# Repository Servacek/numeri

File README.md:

# Numitronové Hodiny - Numeri

Digitálne hodiny využívajúce na zobrazovanie času staré sovietske numitrony IV-9. Podporujú tiež pripojenie rádiového modulu DCF77 pre automatické nastavovanie času podľa atomových hodín z Mainflingenu.

https://github.com/user-attachments/assets/5947127a-6d7e-4e79-9d8d-92cfa04d009d

## DCF77 Anténa

Vlastná 140 mm anténa sa zdá byť najefektívnejšie a cenovo najdostupnejšie riešenie. Čim väčšia feritová tyč, tým lepšie.

## Schéma zapojeniaa návrh plošného spoja

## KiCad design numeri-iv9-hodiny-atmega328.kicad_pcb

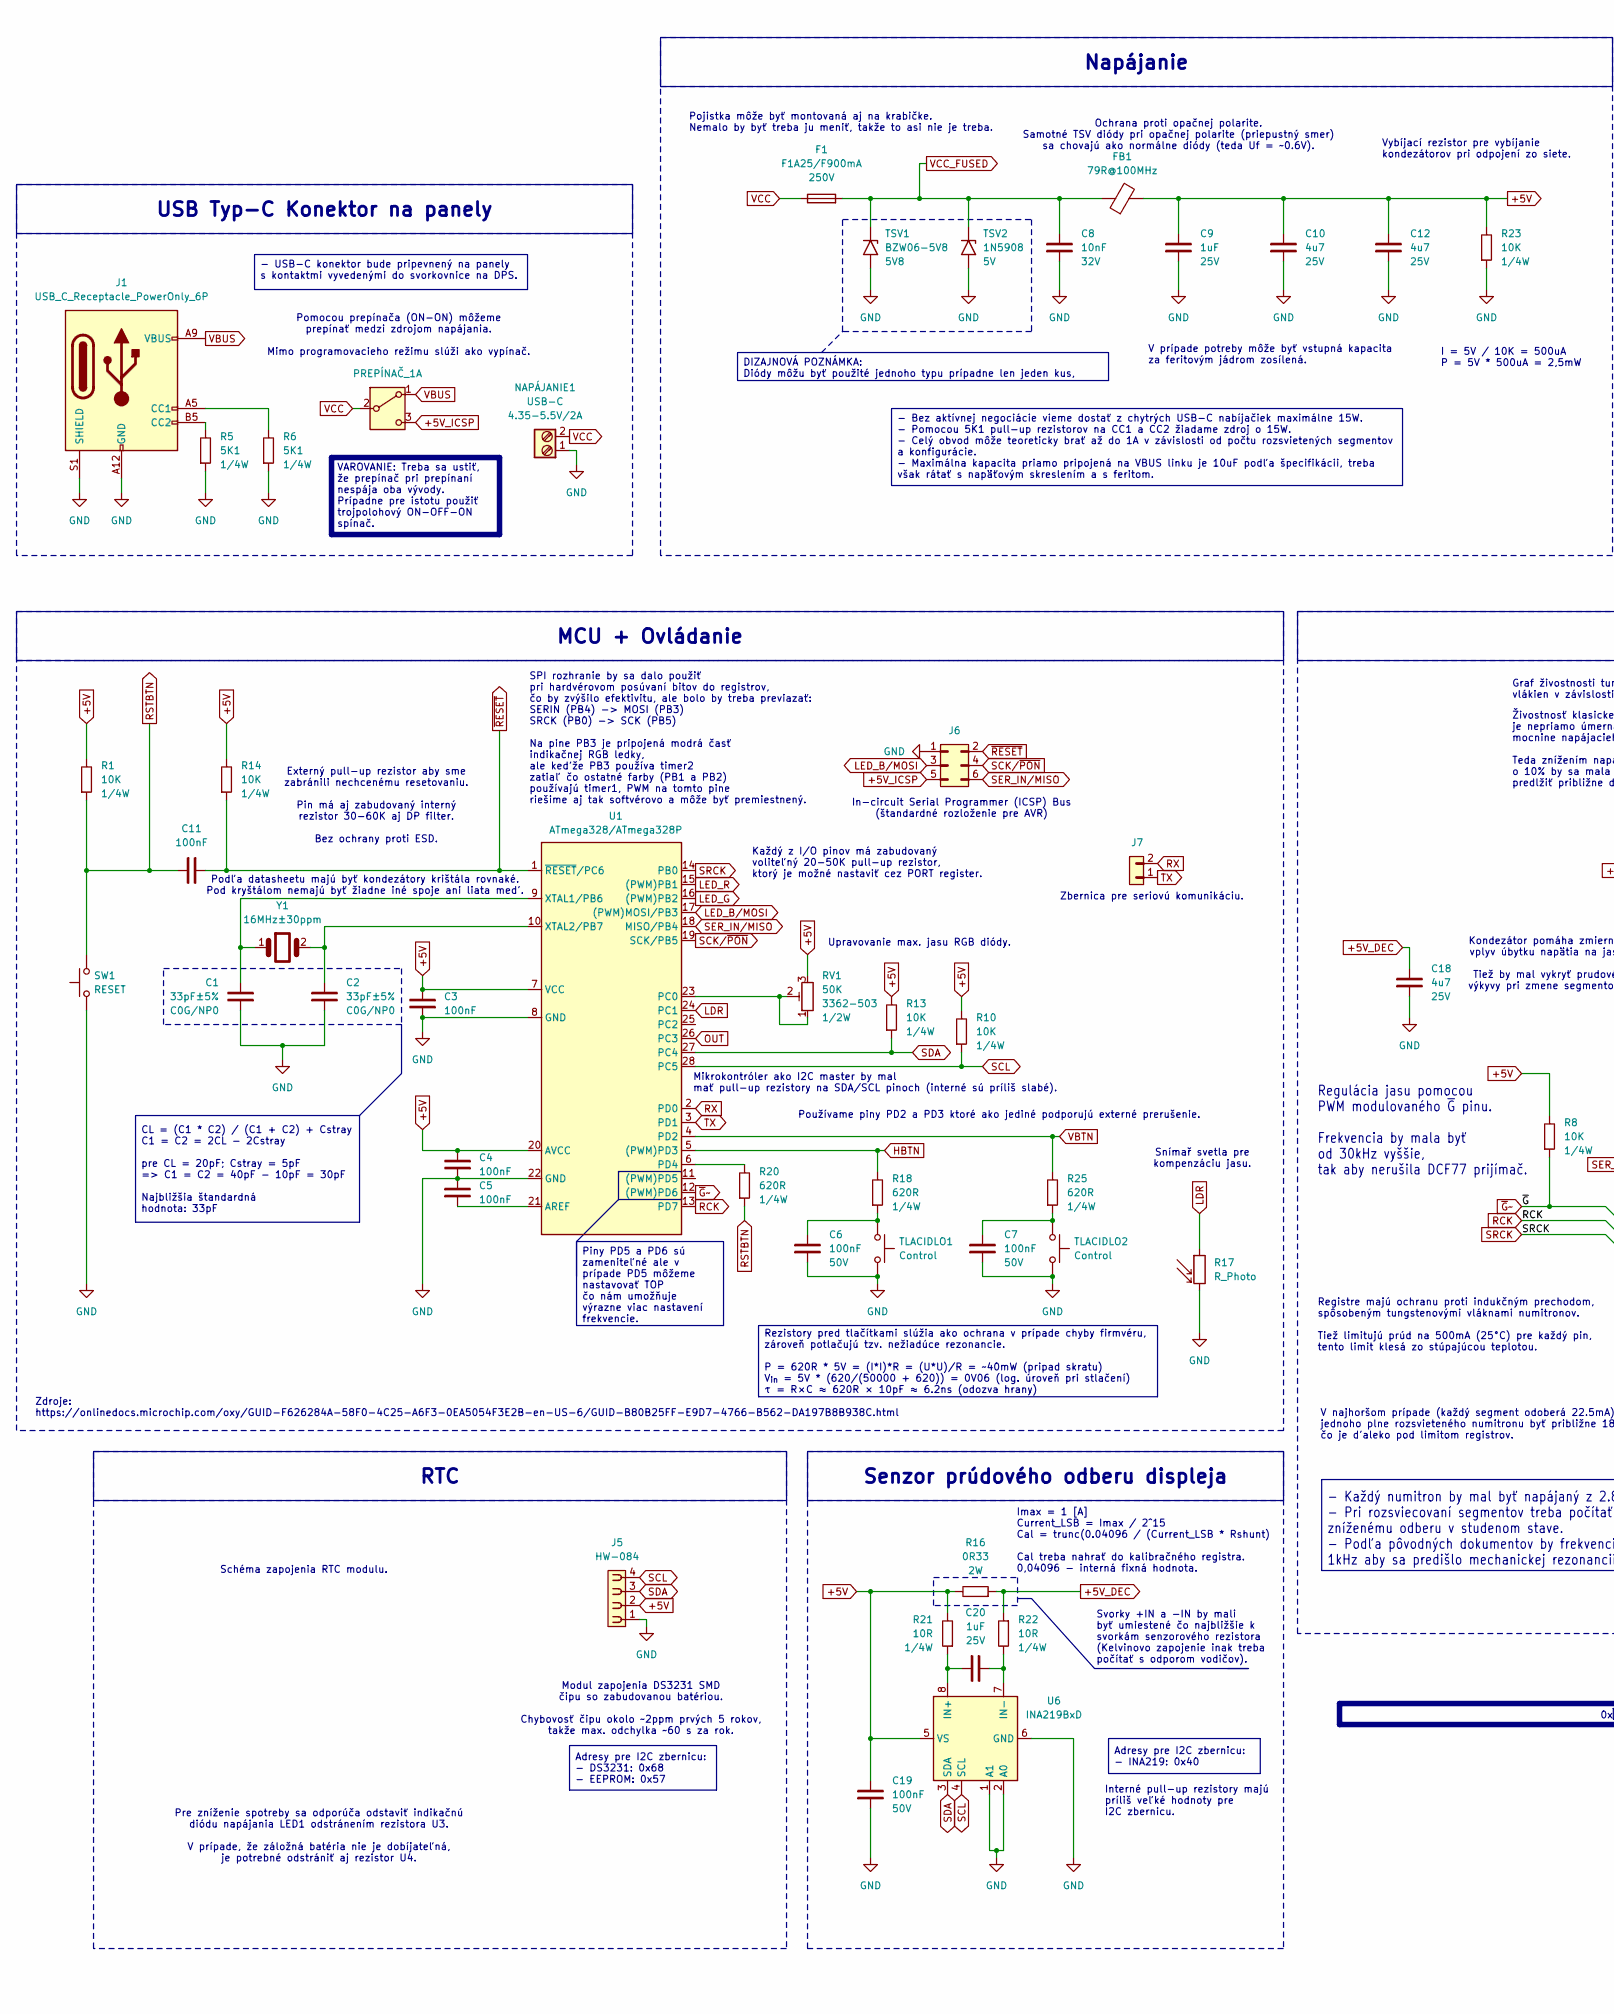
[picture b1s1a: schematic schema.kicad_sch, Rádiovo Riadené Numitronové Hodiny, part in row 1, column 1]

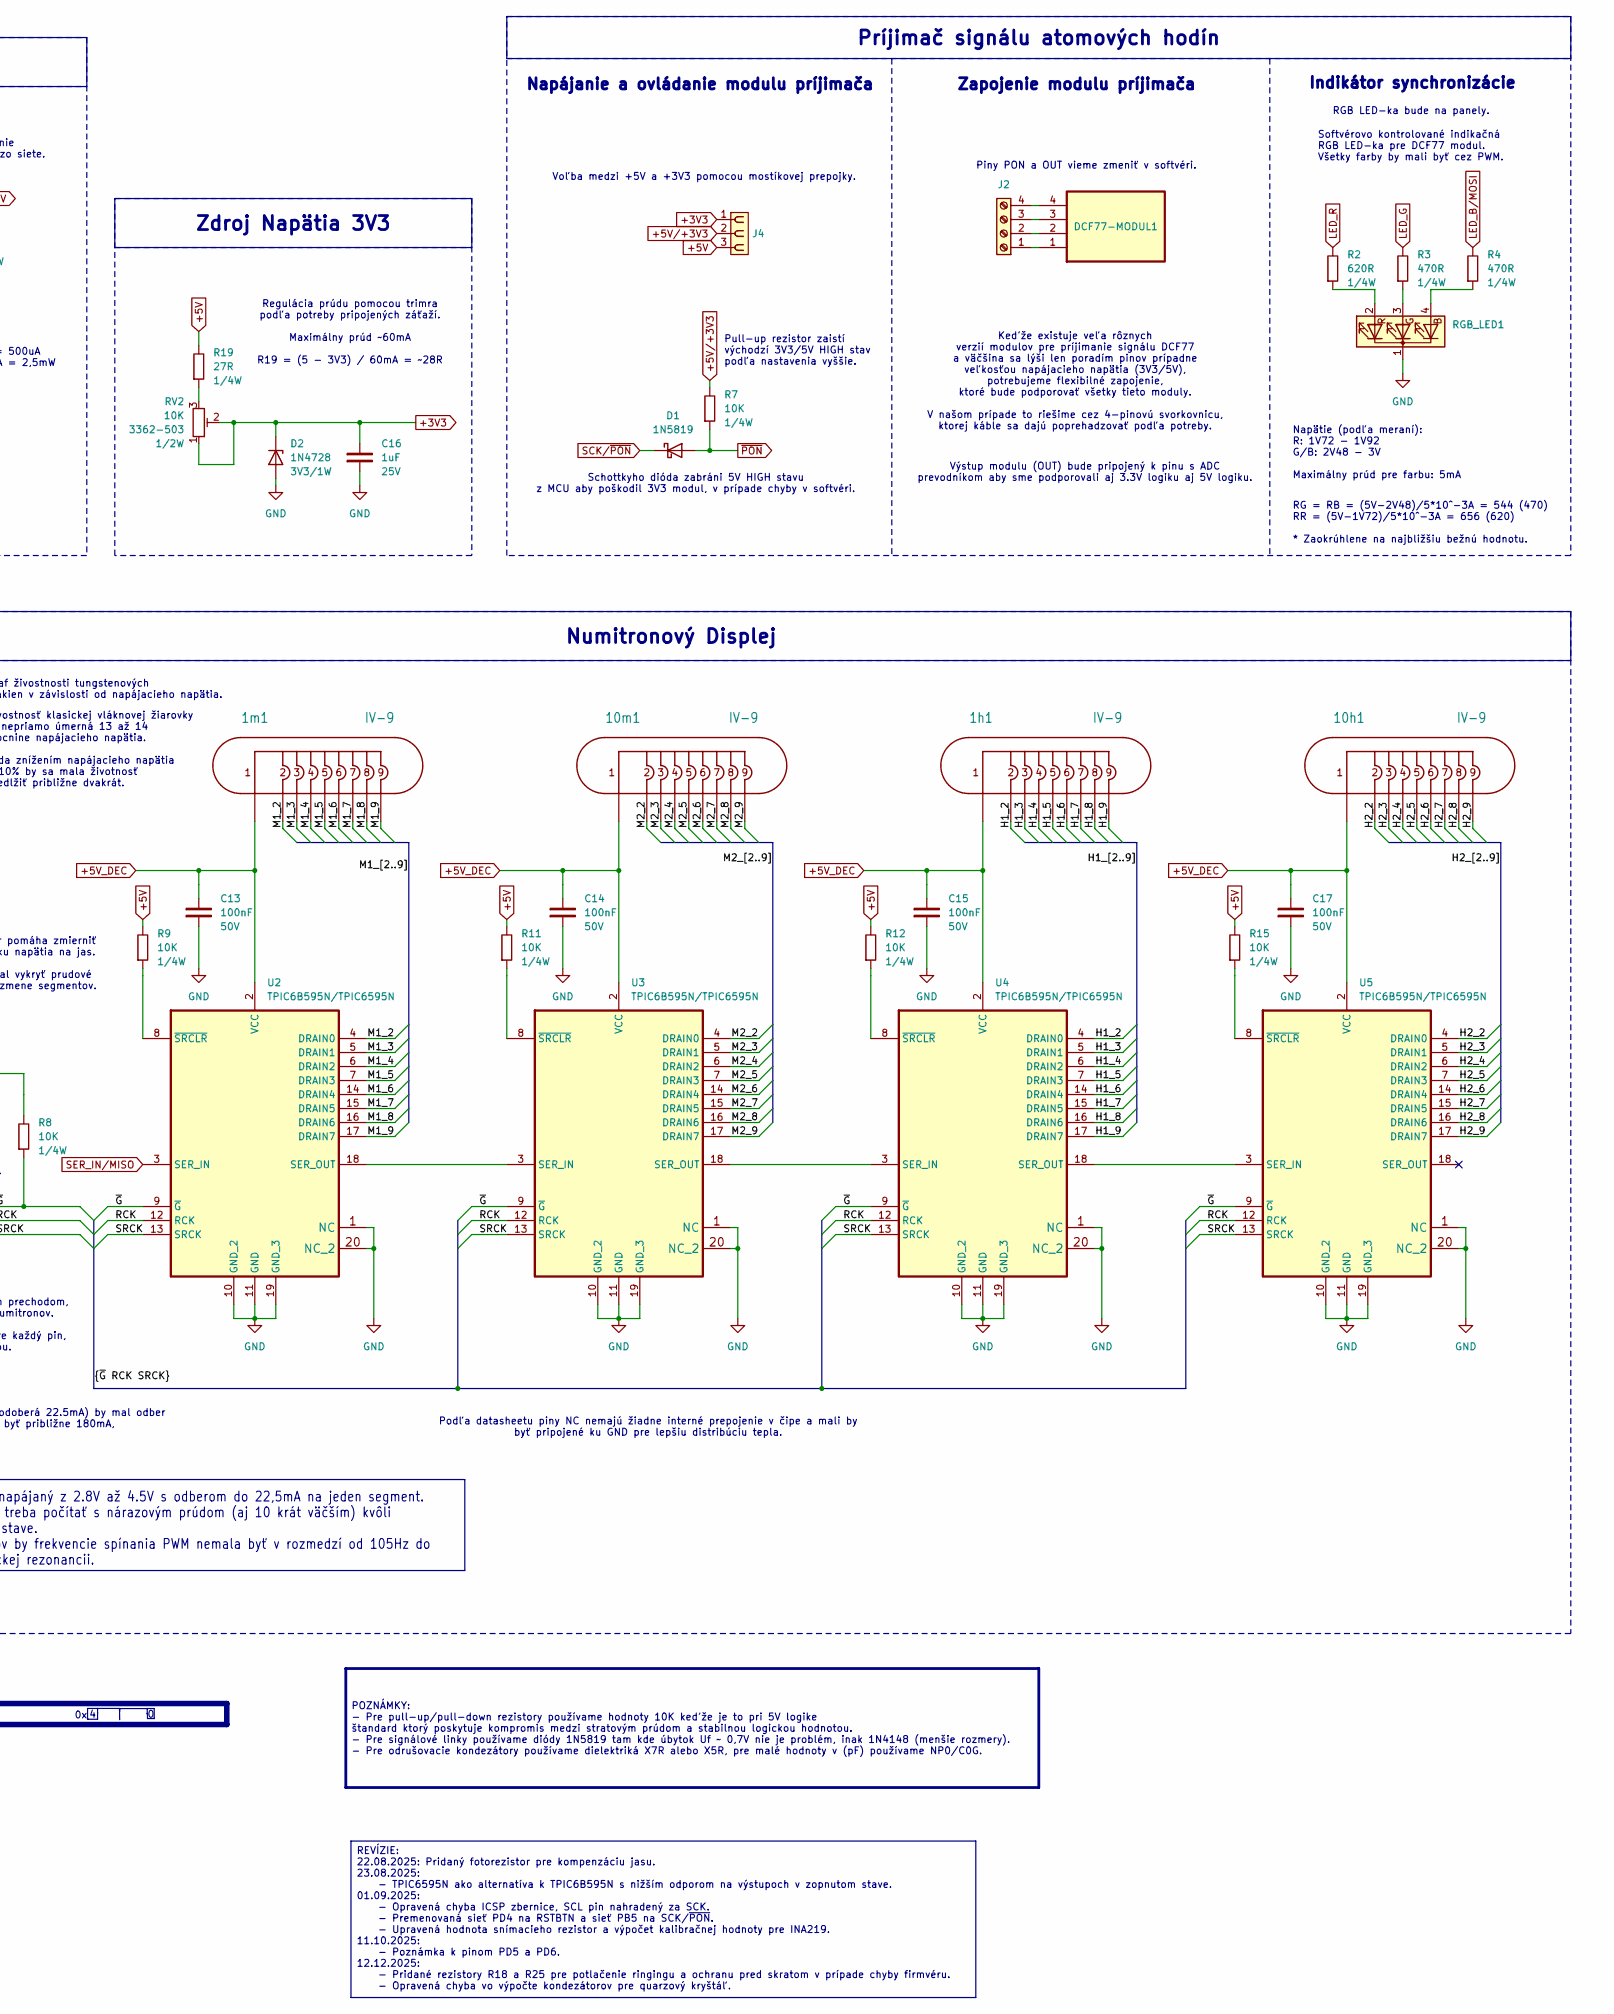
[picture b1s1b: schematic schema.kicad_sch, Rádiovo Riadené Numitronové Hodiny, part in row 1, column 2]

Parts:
1h1, 1m1, 10h1, 10m1: IV-9; IV-9_External_Socket_Asymetric
C1, C2: 33pF±5%; C_Disc_D6.0mm_W2.5mm_P5.00mm
C3, C4, C5, C6, C7, C11, C13, C14, C15, C17, C19: 100nF; C_Disc_D6.0mm_W2.5mm_P5.00mm
C8: 10nF; C_Disc_D6.0mm_W2.5mm_P5.00mm
C9, C16, C20: 1uF; C_Disc_D6.0mm_W2.5mm_P5.00mm
C10, C12, C18: 4u7; C_Disc_D6.0mm_W2.5mm_P5.00mm
D1: 1N5819; D_DO-41_SOD81_P7.62mm_Horizontal
D2: 1N4728; D_DO-35_SOD27_P7.62mm_Horizontal
DCF77-MODUL1: DCF77; PinSocket_1x04_P2.54mm_Vertical
F1: F1A25/F900mA; Fuseholder_Cylinder-5x20mm_Schurter_0031_8201_Horizontal_Op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; Voltage 250V
FB1: 79R@100MHz; L_Axial_L5.0mm_D3.6mm_P10.00mm_Horizontal_Murata_BL01RN1A2A2
J1: USB_C_Receptacle_PowerOnly_6P
J2: Screw_Terminal_01x04; PinSocket_1x04_P2.54mm_Vertical
J4: PINHD_1x3_Female; PinHeader_1x03_P2.54mm_Vertical
J5: HW-084; HW_84
J6: 2x3; PinHeader_2x03_P2.54mm_Vertical
J7: 1x2; PinSocket_1x02_P2.54mm_Vertical
NAPÁJANIE1: USB-C; TerminalBlock_Phoenix_PT-1,5-2-5.0-H_1x02_P5.00mm_Horizontal
PREPÍNAČ_1: SW_DPDT_x2
R1, R8, R9, R11, R12, R14, R15: 10K; R_Axial_DIN0207_L6.3mm_D2.5mm_P7.62mm_Horizontal
R2, R18, R20, R25: 620R; R_Axial_DIN0207_L6.3mm_D2.5mm_P7.62mm_Horizontal
R3, R4: 470R; R_Axial_DIN0207_L6.3mm_D2.5mm_P7.62mm_Horizontal
R5, R6: 5K1; R_Axial_DIN0207_L6.3mm_D2.5mm_P10.16mm_Horizontal
R7: 10K; R_Axial_DIN0207_L6.3mm_D2.5mm_P15.24mm_Horizontal
R10, R13: 10K; R_Axial_DIN0207_L6.3mm_D2.5mm_P5.08mm_Vertical
R16: 0R33; R_Axial_DIN0414_L11.9mm_D4.5mm_P20.32mm_Horizontal
R17: R_Photo
R19: 27R; R_Axial_DIN0207_L6.3mm_D2.5mm_P10.16mm_Horizontal
R21, R22: 10R; R_Axial_DIN0207_L6.3mm_D2.5mm_P7.62mm_Horizontal
R23: 10K; R_Axial_DIN0207_L6.3mm_D2.5mm_P10.16mm_Horizontal
RGB_LED1: RGB_LED; JST_XH_B4B-XH-A_1x04_P2.50mm_Vertical
RV1: 50K; potentiometer_3362P
RV2: 10K; potentiometer_3362P
SW1: RESET; SW_PUSH_6mm
TLACIDLO1, TLACIDLO2: Control; TerminalBlock_Phoenix_PT-1,5-2-5.0-H_1x02_P5.00mm_Horizontal
TSV1: BZW06-5V8; D_DO-15_P12.70mm_Horizontal; Voltage 5V8
TSV2: 1N5908; D_DO-15_P12.70mm_Horizontal; Voltage 5V
U1: ATmega328/ATmega328P; DIP-28_W7.62mm_Socket
U2, U3, U4, U5: TPIC6B595N/TPIC6595N; DIP-20_W7.62mm_Socket_With_IC
U6: INA219BxD; SOIC-8_3.9x4.9mm_P1.27mm
Y1: 16MHz±30ppm; Crystal_HC49-4H_Vertical

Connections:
+3V3: C16.2, D2.1 (K), J4.1, RV2.1, RV2.2
+5V: C3.2, C4.2, C9.2, C10.2, C12.2, C19.2, FB1.2, J4.3, J5.2, R1.2, R8.2, R9.2, R10.2, R11.2, R12.2, R13.2, R14.2, R15.2, R16.2, R19.2, R21.2, R23.2, RV1.3, U1.7 (VCC), U1.20 (AVCC), U6.5 (VS)
+5V_DEC: 1h1.1, 1m1.1, 10h1.1, 10m1.1, C13.2, C14.2, C15.2, C17.2, C18.2, R16.1, R22.1, U2.2 (VCC), U3.2 (VCC), U4.2 (VCC), U5.2 (VCC)
+5V_ICSP: J6.5, PREPÍNAČ_1.3 (C)
+5V/+3V3: J4.2, R7.2
/Hlavná Schéma/H1_2: 1h1.2, U4.4 (DRAIN0)
/Hlavná Schéma/H1_3: 1h1.3, U4.5 (DRAIN1)
/Hlavná Schéma/H1_4: 1h1.4, U4.6 (DRAIN2)
/Hlavná Schéma/H1_5: 1h1.5, U4.7 (DRAIN3)
/Hlavná Schéma/H1_6: 1h1.6, U4.14 (DRAIN4)
/Hlavná Schéma/H1_7: 1h1.7, U4.15 (DRAIN5)
/Hlavná Schéma/H1_8: 1h1.8, U4.16 (DRAIN6)
/Hlavná Schéma/H1_9: 1h1.9, U4.17 (DRAIN7)
/Hlavná Schéma/H2_2: 10h1.2, U5.4 (DRAIN0)
/Hlavná Schéma/H2_3: 10h1.3, U5.5 (DRAIN1)
/Hlavná Schéma/H2_4: 10h1.4, U5.6 (DRAIN2)
/Hlavná Schéma/H2_5: 10h1.5, U5.7 (DRAIN3)
/Hlavná Schéma/H2_6: 10h1.6, U5.14 (DRAIN4)
/Hlavná Schéma/H2_7: 10h1.7, U5.15 (DRAIN5)
/Hlavná Schéma/H2_8: 10h1.8, U5.16 (DRAIN6)
/Hlavná Schéma/H2_9: 10h1.9, U5.17 (DRAIN7)
/Hlavná Schéma/M1_2: 1m1.2, U2.4 (DRAIN0)
/Hlavná Schéma/M1_3: 1m1.3, U2.5 (DRAIN1)
/Hlavná Schéma/M1_4: 1m1.4, U2.6 (DRAIN2)
/Hlavná Schéma/M1_5: 1m1.5, U2.7 (DRAIN3)
/Hlavná Schéma/M1_6: 1m1.6, U2.14 (DRAIN4)
/Hlavná Schéma/M1_7: 1m1.7, U2.15 (DRAIN5)
/Hlavná Schéma/M1_8: 1m1.8, U2.16 (DRAIN6)
/Hlavná Schéma/M1_9: 1m1.9, U2.17 (DRAIN7)
/Hlavná Schéma/M2_2: 10m1.2, U3.4 (DRAIN0)
/Hlavná Schéma/M2_3: 10m1.3, U3.5 (DRAIN1)
/Hlavná Schéma/M2_4: 10m1.4, U3.6 (DRAIN2)
/Hlavná Schéma/M2_5: 10m1.5, U3.7 (DRAIN3)
/Hlavná Schéma/M2_6: 10m1.6, U3.14 (DRAIN4)
/Hlavná Schéma/M2_7: 10m1.7, U3.15 (DRAIN5)
/Hlavná Schéma/M2_8: 10m1.8, U3.16 (DRAIN6)
/Hlavná Schéma/M2_9: 10m1.9, U3.17 (DRAIN7)
GND: C1.1, C2.1, C3.1, C4.1, C5.2, C6.1, C7.1, C8.1, C9.1, C10.1, C12.1, C13.1, C14.1, C15.1, C16.1, C17.1, C18.1, C19.1, D2.2 (A), J1.A12 (GND), J1.B12 (GND), J1.S1 (SHIELD), J5.1, J6.1, NAPÁJANIE1.1, R5.1, R6.1, R17.2, R23.1, RGB_LED1.1 (K), SW1.1, TLACIDLO1.1, TLACIDLO2.1, TSV1.2 (A2), TSV2.2 (A2), U1.8 (GND), U1.22 (GND), U2.1 (NC), U2.10 (GND_2), U2.11 (GND), U2.19 (GND_3), U2.20 (NC_2), U3.1 (NC), U3.10 (GND_2), U3.11 (GND), U3.19 (GND_3), U3.20 (NC_2), U4.1 (NC), U4.10 (GND_2), U4.11 (GND), U4.19 (GND_3), U4.20 (NC_2), U5.1 (NC), U5.10 (GND_2), U5.11 (GND), U5.19 (GND_3), U5.20 (NC_2), U6.1 (A1), U6.2 (A0), U6.6 (GND)
HBTN: R18.2, U1.5 ((PWM)PD3)
LDR: R17.1, U1.24 (PC1)
LED_B/MOSI: J6.3, R4.2, U1.17 ((PWM)MOSI/PB3)
LED_G: R3.2, U1.16 ((PWM)PB2)
LED_R: R2.2, U1.15 ((PWM)PB1)
unnamed: C6.2, R18.1, TLACIDLO1.2
unnamed: C7.2, R25.1, TLACIDLO2.2
unnamed: J1.A5 (CC1), R6.2
unnamed: J1.A9 (VBUS), J1.B9 (VBUS), PREPÍNAČ_1.1 (A)
unnamed: J1.B5 (CC2), R5.2
unnamed: DCF77-MODUL1.1, J2.1
unnamed: DCF77-MODUL1.2, J2.2
unnamed: DCF77-MODUL1.3, J2.3
unnamed: DCF77-MODUL1.4, J2.4
unnamed: R19.1, RV2.3
unnamed: R4.1, RGB_LED1.4 (BA)
unnamed: R3.1, RGB_LED1.3 (GA)
unnamed: R2.1, RGB_LED1.2 (RA)
unnamed: C5.1, U1.21 (AREF)
unnamed: RV1.1, RV1.2, U1.23 (PC0)
unnamed: R20.2, U1.6 (PD4)
unnamed: C1.2, U1.9 (XTAL1/PB6), Y1.1
unnamed: C2.2, U1.10 (XTAL2/PB7), Y1.2
unnamed: U2.18 (SER_OUT), U3.3 (SER_IN)
unnamed: R9.1, U2.8 (~SRCLR)
unnamed: U3.18 (SER_OUT), U4.3 (SER_IN)
unnamed: R11.1, U3.8 (~SRCLR)
unnamed: U4.18 (SER_OUT), U5.3 (SER_IN)
unnamed: R12.1, U4.8 (~SRCLR)
unnamed: R15.1, U5.8 (~SRCLR)
unnamed: C20.1, R21.1, U6.8 (IN+)
unnamed: C20.2, R22.2, U6.7 (IN-)
OUT: U1.26 (PC3)
RCK: U1.13 (PD7), U2.12 (RCK), U3.12 (RCK), U4.12 (RCK), U5.12 (RCK)
RSTBTN: C11.2, R1.1, R20.1, SW1.2
RX: J7.2, U1.2 (PD0)
SCK/~PON: D1.1 (K), J6.4, U1.19 (SCK/PB5)
SCL: J5.4, R10.1, U1.28 (PC5), U6.4 (SCL)
SDA: J5.3, R13.1, U1.27 (PC4), U6.3 (SDA)
SER_IN/MISO: J6.6, U1.18 (MISO/PB4), U2.3 (SER_IN)
SRCK: U1.14 (PB0), U2.13 (SRCK), U3.13 (SRCK), U4.13 (SRCK), U5.13 (SRCK)
TX: J7.1, U1.3 (PD1)
VBTN: R25.2, U1.4 (PD2)
VCC: F1.1, NAPÁJANIE1.2, PREPÍNAČ_1.2 (B)
VCC_FUSED: C8.2, F1.2, FB1.1, TSV1.1 (A1), TSV2.1 (A1)
~G~: R8.1, U1.12 ((PWM)PD6), U2.9 (~G), U3.9 (~G), U4.9 (~G), U5.9 (~G)
~PON: D1.2 (A), R7.1
~RESET: C11.1, J6.2, R14.1, U1.1 (~RESET/PC6)

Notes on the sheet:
Napätie (podľa meraní): R: 1V72 - 1V92 G/B: 2V48 - 3V Maximálny prúd pre farbu: 5mA
Svorky +IN a -IN by mali byť umiestené čo najbližšie k svorkám senzorového rezistora (Kelvinovo zapojenie inak treba počítať s odporom vodičov).
Mikrokontróler ako I2C master by mal mať pull-up rezistory na SDA/SCL pinoch (interné sú príliš slabé).
Zbernica pre seriovú komunikáciu.
Piny PON a OUT vieme zmeniť v softvéri.
Voľba medzi +5V a +3V3 pomocou mostíkovej prepojky.
Snímař svetla pre kompenzáciu jasu.
Výstup modulu (OUT) bude pripojený k pinu s ADC prevodníkom aby sme podporovali aj 3.3V logiku aj 5V logiku.
Regulácia jasu pomocou PWM modulovaného ~{G} pinu. Frekvencia by mala byť od 30kHz vyššie, tak aby nerušila DCF77 prijímač.
Indikátor synchronizácie
Každý z I/O pinov má zabudovaný voliteľný 20-50K pull-up rezistor, ktorý je možné nastaviť cez PORT register.
Pojistka môže byť montovaná aj na krabičke. Nemalo by byť treba ju meniť, takže to asi nie je treba.
V najhoršom prípade (každý segment odoberá 22.5mA) by mal odber jednoho plne rozsvieteného numitronu byť približne 180mA, čo je ďaleko pod limitom registrov.
Napájanie a ovládanie modulu príjimača
Ochrana proti opačnej polarite. Samotné TSV diódy pri opačnej polarite (priepustný smer) sa chovajú ako normálne diódy (teda Uf = ~0.6V).
Zdroje: https://onlinedocs.microchip.com/oxy/GUID-F626284A-58F0-4C25-A6F3-0EA5054F3E2B-en-US-6/GUID-B80B25FF-E9D7-4766-B562-DA197B8B938C.html
RGB LED-ka bude na panely.
Imax = 1 [A] Current_LSB = Imax / 2^15 Cal = trunc(0.04096 / (Current_LSB * Rshunt) Cal treba nahrať do kalibračného registra. 0,04096 - interná fixná hodnota.
Pre zníženie spotreby sa odporúča odstaviť indikačnú diódu napájania LED1 odstránením rezistora U3. V prípade, že záložná batéria nie je dobíjateľná, je potrebné odstrániť aj rezistor U4.
In-circuit Serial Programmer (ICSP) Bus (štandardné rozloženie pre AVR)
I = 5V / 10K = 500uA P = 5V * 500uA = 2,5mW
Podľa datasheetu majú byť kondezátory krištála rovnaké. Pod kryštálom nemajú byť žiadne iné spoje ani liata meď.
Živostnosť klasickej vláknovej žiarovky je nepriamo úmerná 13 až 14 mocnine napájacieho napätia. Teda znížením napájacieho napätia o 10% by sa mala životnosť predlžiť približne dvakrát.
Vybíjací rezistor pre vybíjanie kondezátorov pri odpojení zo siete.
SPI rozhranie by sa dalo použiť pri hardvérovom posúvaní bitov do registrov, čo by zvýšilo efektivitu, ale bolo by treba previazať: SERIN (PB4) -> MOSI (PB3) SRCK (PB0) -> SCK (PB5) Na pine PB3 je pripojená modrá časť indikačnej RGB ledky, ale keďže PB3 používa timer2 zatiaľ čo ostatné farby (PB1 a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
Upravovanie max. jasu RGB diódy.
Registre majú ochranu proti indukčným prechodom, spôsobeným tungstenovými vláknami numitronov. Tiež limitujú prúd na 500mA (25°C) pre každý pin, tento limit klesá zo stúpajúcou teplotou.
Keďže existuje veľa rôznych verzií modulov pre príjimanie signálu DCF77 a väčšina sa lýši len poradím pinov prípadne veľkosťou napájacieho napätia (3V3/5V), potrebujeme flexibilné zapojenie, ktoré bude podporovať všetky tieto moduly. V našom prípade to riešime cez 4-pinovú svorkovnicu, ktorej káble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
Pomocou prepínača (ON-ON) môžeme prepínať medzi zdrojom napájania. Mimo programovacieho režimu slúži ako vypínač.
Interné pull-up rezistory majú príliš veľké hodnoty pre I2C zbernicu.
Regulácia prúdu pomocou trimra podľa potreby pripojených záťaží. Maximálny prúd ~60mA R19 = (5 - 3V3) / 60mA = ~28R
RG = RB = (5V-2V48)/5*10^-3A = 544 (470) RR = (5V-1V72)/5*10^-3A = 656 (620) * Zaokrúhlene na najbližšiu bežnú hodnotu.
Schéma zapojenia RTC modulu.
Pull-up rezistor zaistí východzí 3V3/5V HIGH stav podľa nastavenia vyššie.
Externý pull-up rezistor aby sme zabránili nechcenému resetovaniu. Pin má aj zabudovaný interný rezistor 30-60K aj DP filter. Bez ochrany proti ESD.
Zapojenie modulu príjimača
Kondezátor pomáha zmierniť vplyv úbytku napätia na jas. Tiež by mal vykryť prudové výkyvy pri zmene segmentov.
Graf živostnosti tungstenových vlákien v závislosti od napájacieho napätia.
Používame piny PD2 a PD3 ktoré ako jediné podporujú externé prerušenie.
V prípade potreby môže byť vstupná kapacita za feritovým jádrom zosílená.

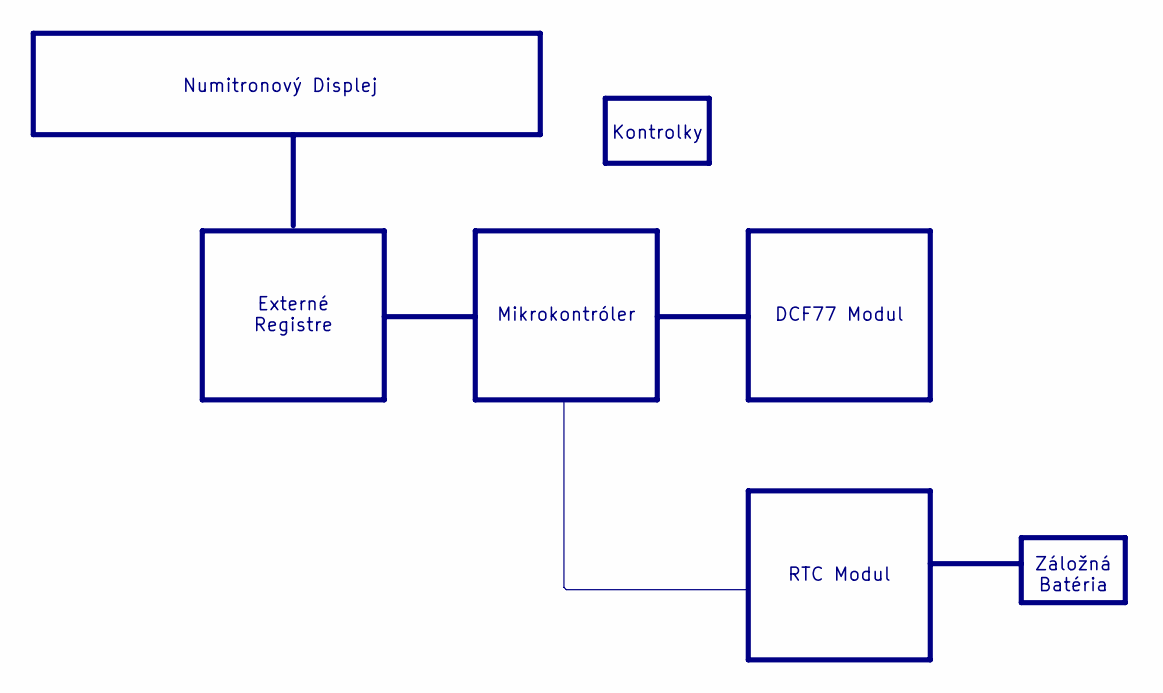
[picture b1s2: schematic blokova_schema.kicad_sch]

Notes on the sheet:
Externé Registre
Kontrolky
Numitronový Displej
DCF77 Modul
Záložná Batéria
RTC Modul
Mikrokontróler

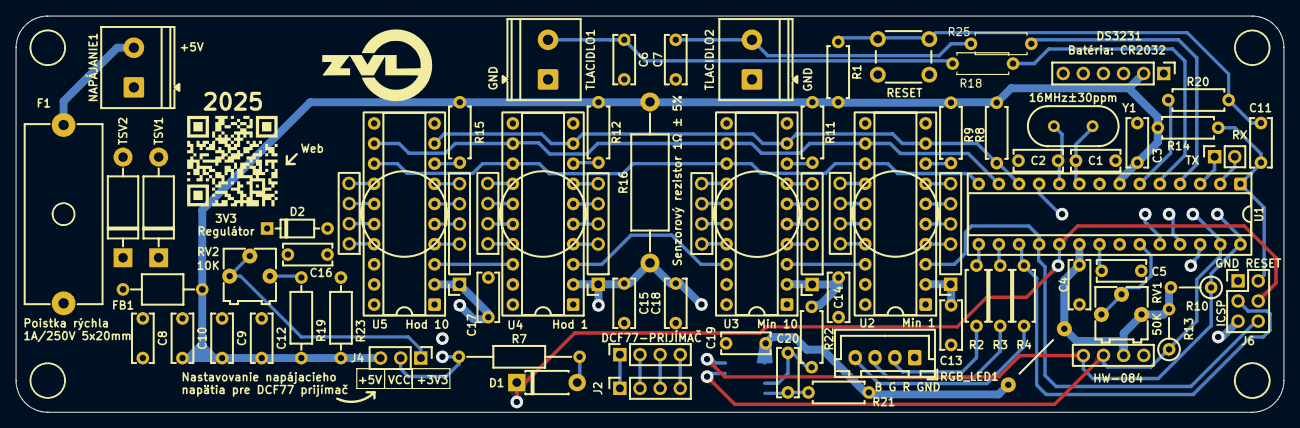
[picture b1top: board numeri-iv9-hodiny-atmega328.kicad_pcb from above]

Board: 2 copper layers, 160.0 x 50.0 mm, 71 parts (1 on the bottom side), 80 nets.

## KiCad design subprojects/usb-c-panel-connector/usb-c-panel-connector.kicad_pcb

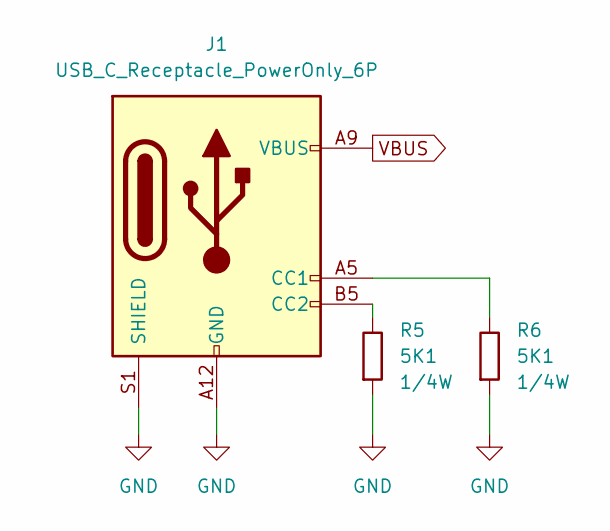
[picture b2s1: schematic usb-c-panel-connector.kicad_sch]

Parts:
J1: USB_C_Receptacle_PowerOnly_6P; USB_C_Receptacle_GCT_USB4125-xx-x-0190_6P_TopMnt_Horizontal
R5, R6: 5K1; R_1206_3216Metric

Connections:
GND: J1.A12 (GND), J1.B12 (GND), J1.S1 (SHIELD), R5.1, R6.1
unnamed: J1.A5 (CC1), R6.2
unnamed: J1.B5 (CC2), R5.2
VBUS: J1.A9 (VBUS), J1.B9 (VBUS)

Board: 2 copper layers, 3 parts (0 on the bottom side), 4 nets, no tracks yet.

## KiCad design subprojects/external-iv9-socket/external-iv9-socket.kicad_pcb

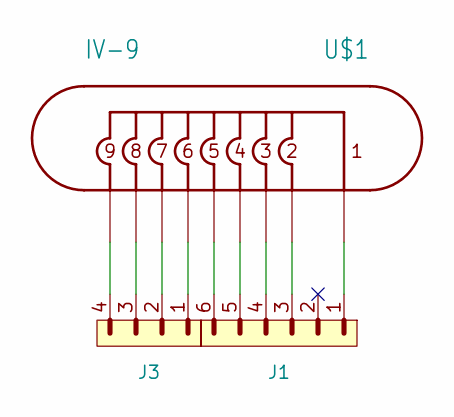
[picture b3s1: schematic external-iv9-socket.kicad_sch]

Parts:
J1: PINHD_1x6_Male; PinHeader_1x06_P2.54mm_Vertical
J3: PINHD_1x4_Male; PinHeader_1x04_P2.54mm_Vertical_MONO
U$1: IV-9; IV-9-Common-Separated

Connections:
unnamed: J1.1, U$1.1
unnamed: J1.3, U$1.2
unnamed: J1.4, U$1.3
unnamed: J1.5, U$1.4
unnamed: J1.6, U$1.5
unnamed: J3.1, U$1.6
unnamed: J3.2, U$1.7
unnamed: J3.3, U$1.8
unnamed: J3.4, U$1.9

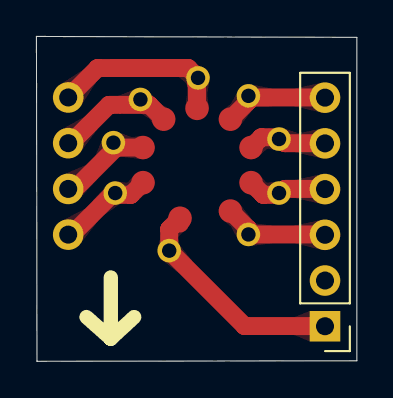
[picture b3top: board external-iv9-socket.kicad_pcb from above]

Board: 2 copper layers, 17.8 x 18.0 mm, 3 parts (1 on the bottom side), 9 nets.
